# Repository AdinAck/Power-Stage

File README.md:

# MonsterFOCer-Power-Stage
 Evaluation board to do R&D for the MonsterFOCer project.

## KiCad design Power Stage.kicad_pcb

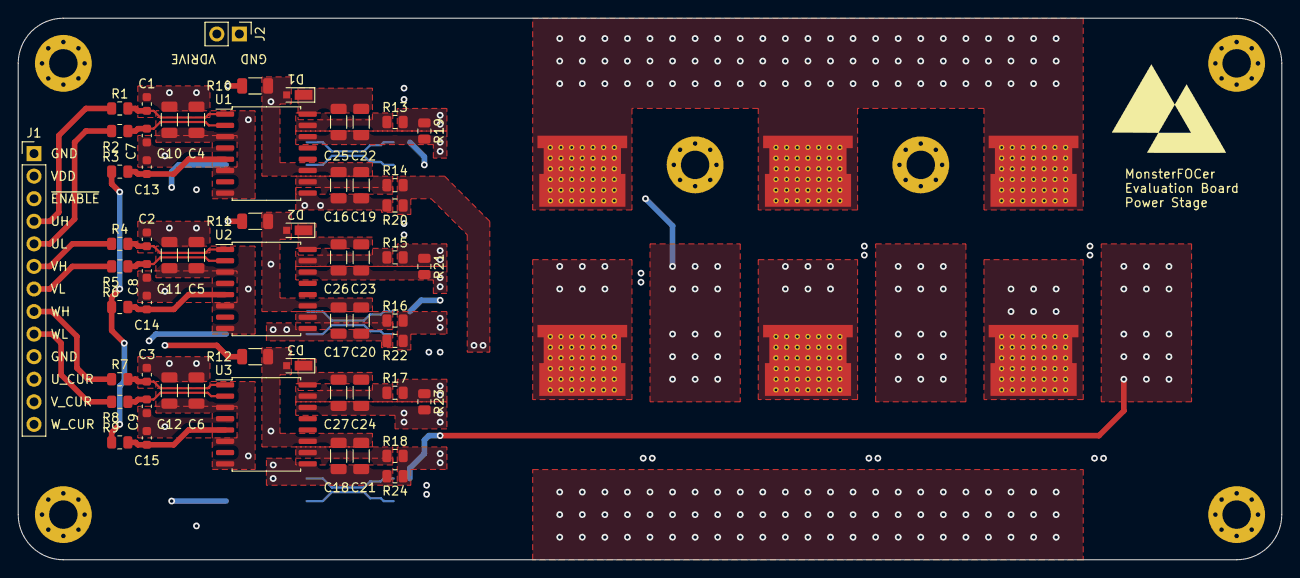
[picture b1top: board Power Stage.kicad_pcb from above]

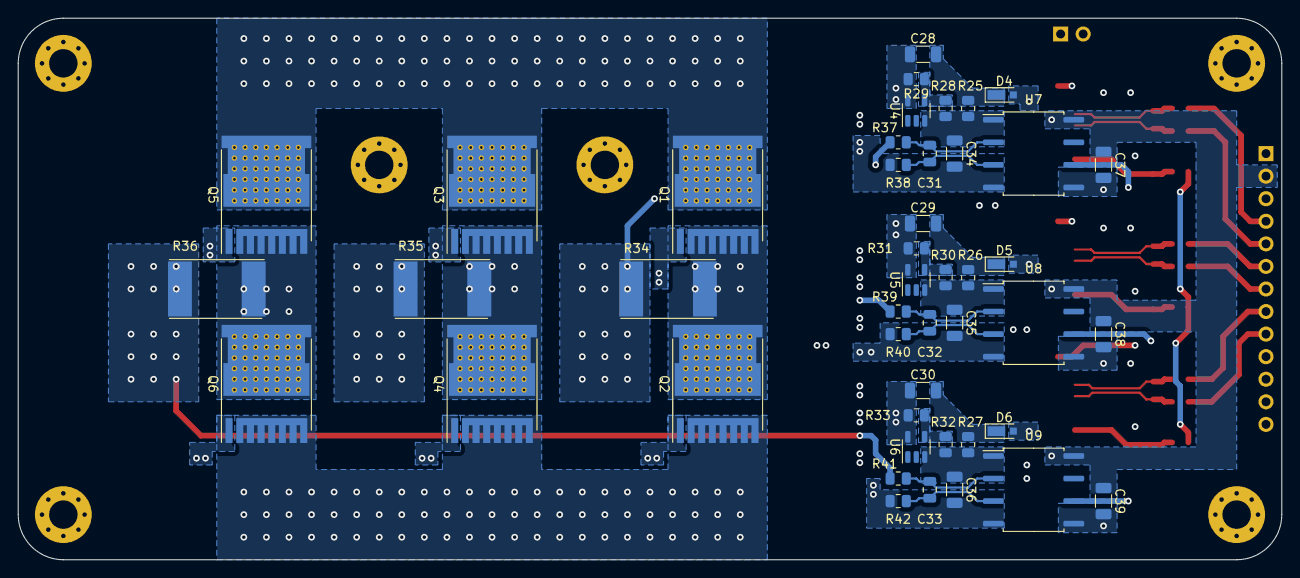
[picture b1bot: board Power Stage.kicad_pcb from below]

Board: 4 copper layers, 142.2 x 61.0 mm, 110 parts (45 on the bottom side), 62 nets.

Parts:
C1, C2, C3, C7, C8, C9, C13, C14, C15: 33p; C_0603_1608Metric
C4, C5, C6, C16, C17, C18, C25, C26, C27, C34, C35, C36, C37, C38, C39: 100n; C_1206_3216Metric
C10, C11, C12, C19, C20, C21, C28, C29, C30: 10u; C_1206_3216Metric
C22, C23, C24: 1u; C_1206_3216Metric
C31, C32, C33: 330p; C_0805_2012Metric
D1, D2, D3, D4, D5, D6: D_Schottky; D_MicroSMP_AK
H1, H2, H3, H4, H5, H6: MountingHole_Pad; MountingHole_3.2mm_M3_Pad_Via
J1: Conn_01x13_Pin; PinHeader_1x13_P2.54mm_Vertical
J2: Conn_01x02_Pin; PinHeader_1x02_P2.54mm_Vertical
Q1, Q2, Q3, Q4, Q5, Q6: IPD70R360P7SAUMA1; Infineon_PG-HSOF-8-1_ThermalVias
R1, R2, R3, R4, R5, R6, R7, R8, R9: 51; R_0805_2012Metric
R10, R11, R12: 1; R_1206_3216Metric
R13, R14, R15, R16, R17, R18: TBD; R_0805_2012Metric
R19, R20, R21, R22, R23, R24, R28, R29, R30, R31, R32, R33: 10k; R_0805_2012Metric
R25, R26, R27: 300; R_0805_2012Metric
R34, R35, R36: 200u; R_Shunt_Bourns_3920
R37, R38, R39, R40, R41, R42: 12; R_0805_2012Metric
U1, U2, U3: UCC21520DW; SOIC-16W_7.5x10.3mm_P1.27mm
U4, U5, U6: TL431DBV; SOT-23-5
U7, U8, U9: AMC1200; SOP-8_6.62x9.15mm_P2.54mm

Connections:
/UH: J1.4, R1.1
/UL: J1.5, R2.1
/U_CUR: J1.11, U7.6 (-)
/U_OUT: R34.2, R37.1
/VH: J1.6, R4.1
/VL: J1.7, R5.1
/V_CUR: J1.12, U8.6 (-)
/V_OUT: R35.2, R39.1
/WH: J1.8, R7.1
/WL: J1.9, R8.1
/W_CUR: J1.13, U9.6 (-)
/W_OUT: R36.2, R41.1
/~ENABLE: J1.3, R3.1, R6.1, R9.1
GND: C1.2, C2.2, C3.2, C4.2, C5.2, C6.2, C7.2, C8.2, C9.2, C10.2, C11.2, C12.2, C13.2, C14.2, C15.2, C16.2, C17.2, C18.2, C19.2, C20.2, C21.2, C37.2, C38.2, C39.2, J1.1, J1.10, J2.1, Q2.2 (S), Q4.2 (S), Q6.2 (S), R20.2, R22.2, R24.2, U1.4 (GND), U1.9 (VSSB), U2.4 (GND), U2.9 (VSSB), U3.4 (GND), U3.9 (VSSB), U7.5 (V-), U8.5 (V-), U9.5 (V-)
unnamed: C31.1, R37.2, U7.2 (+)
unnamed: C31.2, R38.2, U7.3 (-)
unnamed: C32.1, R39.2, U8.2 (+)
unnamed: C32.2, R40.2, U8.3 (-)
unnamed: C33.1, R41.2, U9.2 (+)
unnamed: C33.2, R42.2, U9.3 (-)
unnamed: C16.1, C19.1, D1.2 (A), D4.2 (A), R10.1, U1.11 (VDDB)
unnamed: C22.1, C25.1, D1.1 (K), U1.16 (VDDA)
unnamed: C17.1, C20.1, D2.2 (A), D5.2 (A), R11.1, U2.11 (VDDB)
unnamed: C23.1, C26.1, D2.1 (K), U2.16 (VDDA)
unnamed: C18.1, C21.1, D3.2 (A), D6.2 (A), R12.1, U3.11 (VDDB)
unnamed: C24.1, C27.1, D3.1 (K), U3.16 (VDDA)
unnamed: C28.1, D4.1 (K), R25.1
unnamed: C29.1, D5.1 (K), R26.1
unnamed: C30.1, D6.1 (K), R27.1
unnamed: Q1.1 (G), R13.2, R19.1
unnamed: C22.2, C25.2, C28.2, C34.2, Q1.2 (S), Q2.3 (D), R19.2, R29.2, R34.1, R38.1, U1.14 (VSSA), U4.5 (A), U7.4 (V-)
unnamed: Q2.1 (G), R14.2, R20.1
unnamed: Q3.1 (G), R15.2, R21.1
unnamed: C23.2, C26.2, C29.2, C35.2, Q3.2 (S), Q4.3 (D), R21.2, R31.2, R35.1, R40.1, U2.14 (VSSA), U5.5 (A), U8.4 (V-)
unnamed: Q4.1 (G), R16.2, R22.1
unnamed: Q5.1 (G), R17.2, R23.1
unnamed: C24.2, C27.2, C30.2, C36.2, Q5.2 (S), Q6.3 (D), R23.2, R33.2, R36.1, R42.1, U3.14 (VSSA), U6.5 (A), U9.4 (V-)
unnamed: Q6.1 (G), R18.2, R24.1
unnamed: C13.1, R3.2, U1.5 (DIS)
unnamed: C1.1, R1.2, U1.1 (INA)
unnamed: C7.1, R2.2, U1.2 (INB)
unnamed: R13.1, U1.15 (OUTA)
unnamed: R14.1, U1.10 (OUTB)
unnamed: C14.1, R6.2, U2.5 (DIS)
unnamed: C2.1, R4.2, U2.1 (INA)
unnamed: C8.1, R5.2, U2.2 (INB)
unnamed: R15.1, U2.15 (OUTA)
unnamed: R16.1, U2.10 (OUTB)
unnamed: C15.1, R9.2, U3.5 (DIS)
unnamed: C3.1, R7.2, U3.1 (INA)
unnamed: C9.1, R8.2, U3.2 (INB)
unnamed: R17.1, U3.15 (OUTA)
unnamed: R18.1, U3.10 (OUTB)
unnamed: C34.1, R25.2, R28.1, U4.3 (K), U7.1 (V+)
unnamed: R28.2, R29.1, U4.4 (REF)
unnamed: C35.1, R26.2, R30.1, U5.3 (K), U8.1 (V+)
unnamed: R30.2, R31.1, U5.4 (REF)
unnamed: C36.1, R27.2, R32.1, U6.3 (K), U9.1 (V+)
unnamed: R32.2, R33.1, U6.4 (REF)
VDD: C4.1, C5.1, C6.1, C10.1, C11.1, C12.1, C37.1, C38.1, C39.1, J1.2, U1.3 (VCCI), U1.6 (DT), U1.8 (VCCI), U2.3 (VCCI), U2.6 (DT), U2.8 (VCCI), U3.3 (VCCI), U3.6 (DT), U3.8 (VCCI), U7.8 (V+), U8.8 (V+), U9.8 (V+)
VS: Q1.3 (D), Q3.3 (D), Q5.3 (D)
Vdrive: J2.2, R10.2, R11.2, R12.2
